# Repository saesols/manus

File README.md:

# Aptas Manus

My updated version of the [Lalboard](https://github.com/JesusFreke/lalboard) ergonomic keyboard with:

- cadquery for model generation
- QMK as firmware 
- Docs for keyboard enthusiasts

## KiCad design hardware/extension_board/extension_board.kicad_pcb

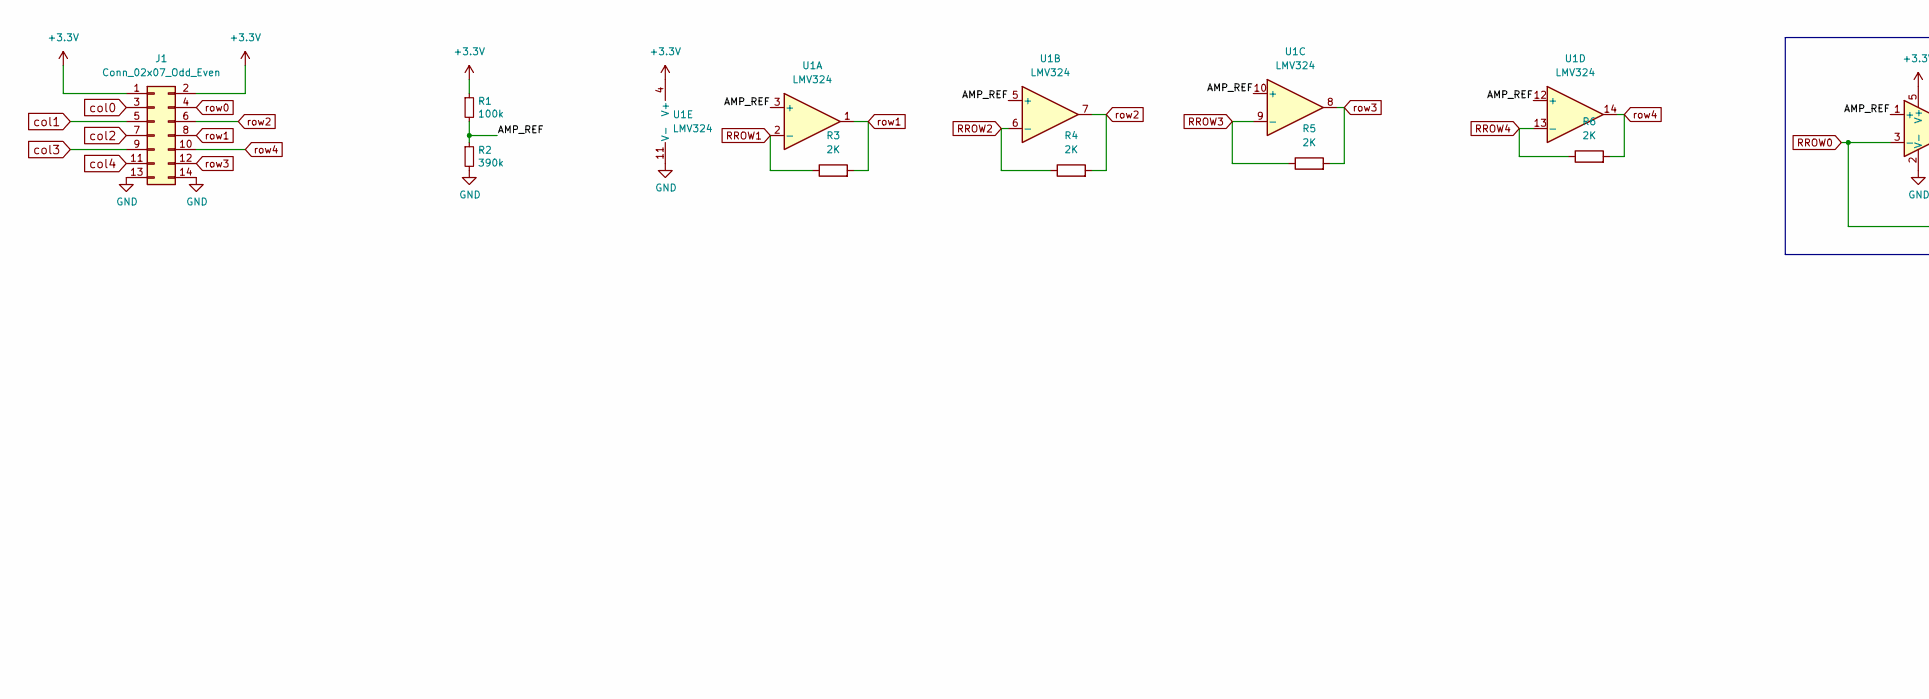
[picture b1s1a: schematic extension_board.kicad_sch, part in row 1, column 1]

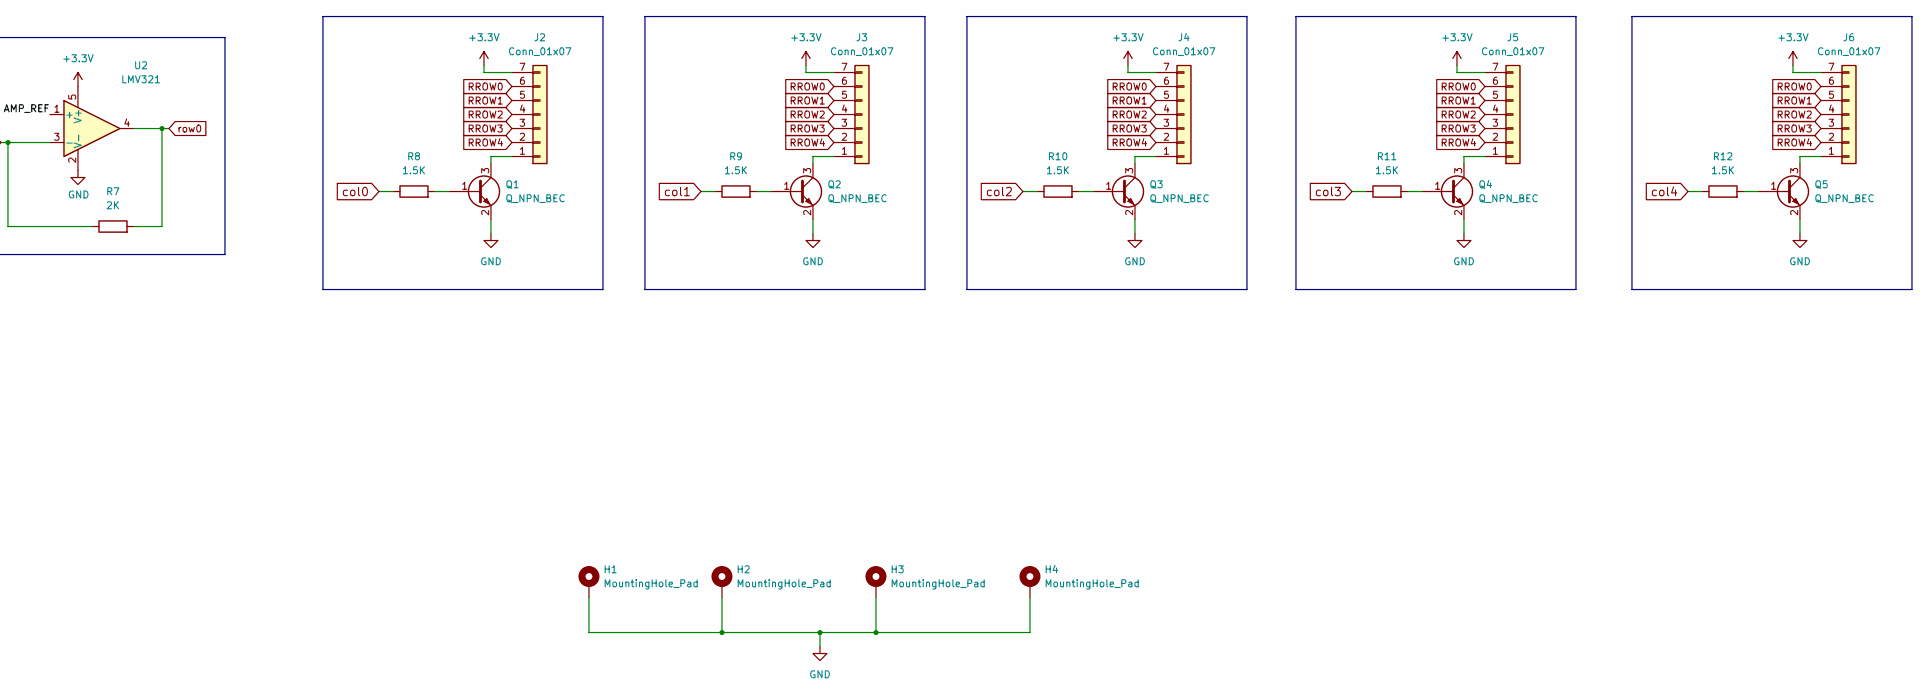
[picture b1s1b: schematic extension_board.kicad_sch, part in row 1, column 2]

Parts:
H1, H2, H3, H4: MountingHole_Pad; MountingHole_3.2mm_M3_DIN965_Pad
J1: Conn_02x07_Odd_Even; IDC-Header_2x07_P2.54mm_Vertical
J2, J3, J4, J5, J6: Conn_01x07; JST_ZH_B7B-ZR_1x07_P1.50mm_Vertical
Q1, Q2, Q3, Q4, Q5: Q_NPN_BEC; SOT-23_Handsoldering
R1: 100k; R_0805_2012Metric_Pad1.20x1.40mm_HandSolder
R2: 390k; R_0805_2012Metric_Pad1.20x1.40mm_HandSolder
R3, R4, R5, R6, R7: 2K; R_0805_2012Metric_Pad1.20x1.40mm_HandSolder
R8, R9, R10, R11, R12: 1.5K; R_0805_2012Metric_Pad1.20x1.40mm_HandSolder
U1: LMV324; SOIC-14_3.9x8.7mm_P1.27mm
U2: LMV321; SOT-23-5_HandSoldering

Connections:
+3V3: J1.1, J1.2, J2.7, J3.7, J4.7, J5.7, J6.7, R1.1, U1.4 (V+), U2.5 (V+)
/AMP_REF: R1.2, R2.1, U1.3 (+), U1.5 (+), U1.10 (+), U1.12 (+), U2.1 (+)
GND: H1.1, H2.1, H3.1, H4.1, J1.13, J1.14, Q1.2 (E), Q2.2 (E), Q3.2 (E), Q4.2 (E), Q5.2 (E), R2.2, U1.11 (V-), U2.2 (V-)
unnamed: J2.1, Q1.3 (C)
unnamed: J3.1, Q2.3 (C)
unnamed: J4.1, Q3.3 (C)
unnamed: J5.1, Q4.3 (C)
unnamed: J6.1, Q5.3 (C)
unnamed: Q1.1 (B), R8.2
unnamed: Q2.1 (B), R9.2
unnamed: Q3.1 (B), R10.2
unnamed: Q4.1 (B), R11.2
unnamed: Q5.1 (B), R12.2
RROW0: J2.6, J3.6, J4.6, J5.6, J6.6, R7.1, U2.3 (-)
RROW1: J2.5, J3.5, J4.5, J5.5, J6.5, R3.1, U1.2 (-)
RROW2: J2.4, J3.4, J4.4, J5.4, J6.4, R4.1, U1.6 (-)
RROW3: J2.3, J3.3, J4.3, J5.3, J6.3, R5.1, U1.9 (-)
RROW4: J2.2, J3.2, J4.2, J5.2, J6.2, R6.1, U1.13 (-)
col0: J1.3, R8.1
col1: J1.5, R9.1
col2: J1.7, R10.1
col3: J1.9, R11.1
col4: J1.11, R12.1
row0: J1.4, R7.2, U2.4
row1: J1.8, R3.2, U1.1
row2: J1.6, R4.2, U1.7
row3: J1.12, R5.2, U1.8
row4: J1.10, R6.2, U1.14

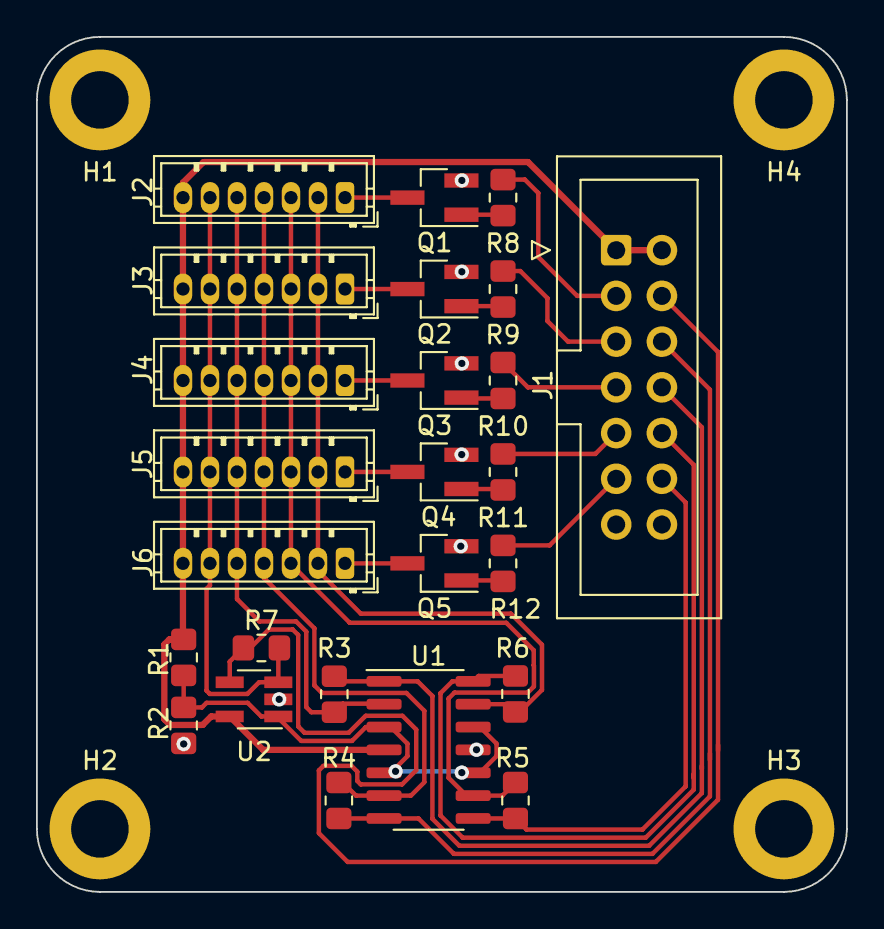
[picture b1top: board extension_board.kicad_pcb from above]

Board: 2 copper layers, 45.0 x 47.5 mm, 29 parts (0 on the bottom side), 28 nets.

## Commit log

2022-06-11 create extension board
